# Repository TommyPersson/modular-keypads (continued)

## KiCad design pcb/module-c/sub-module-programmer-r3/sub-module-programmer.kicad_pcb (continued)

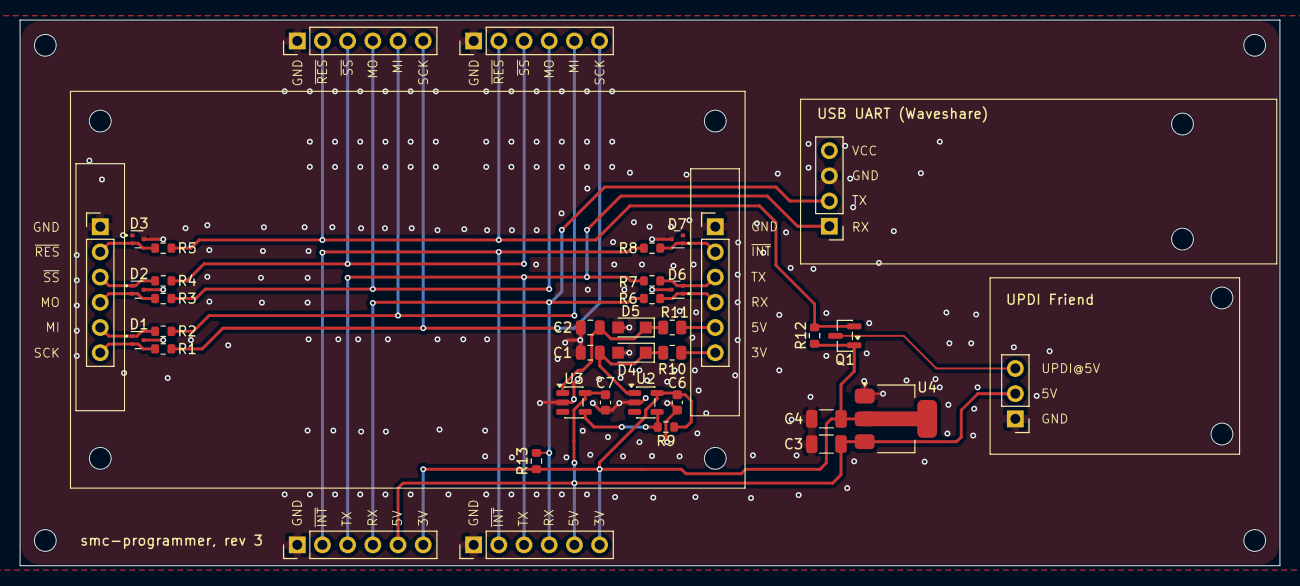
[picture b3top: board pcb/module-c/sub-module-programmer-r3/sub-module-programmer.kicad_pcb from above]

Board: 4 copper layers, 127.0 x 55.0 mm, 50 parts (0 on the bottom side), 25 nets.

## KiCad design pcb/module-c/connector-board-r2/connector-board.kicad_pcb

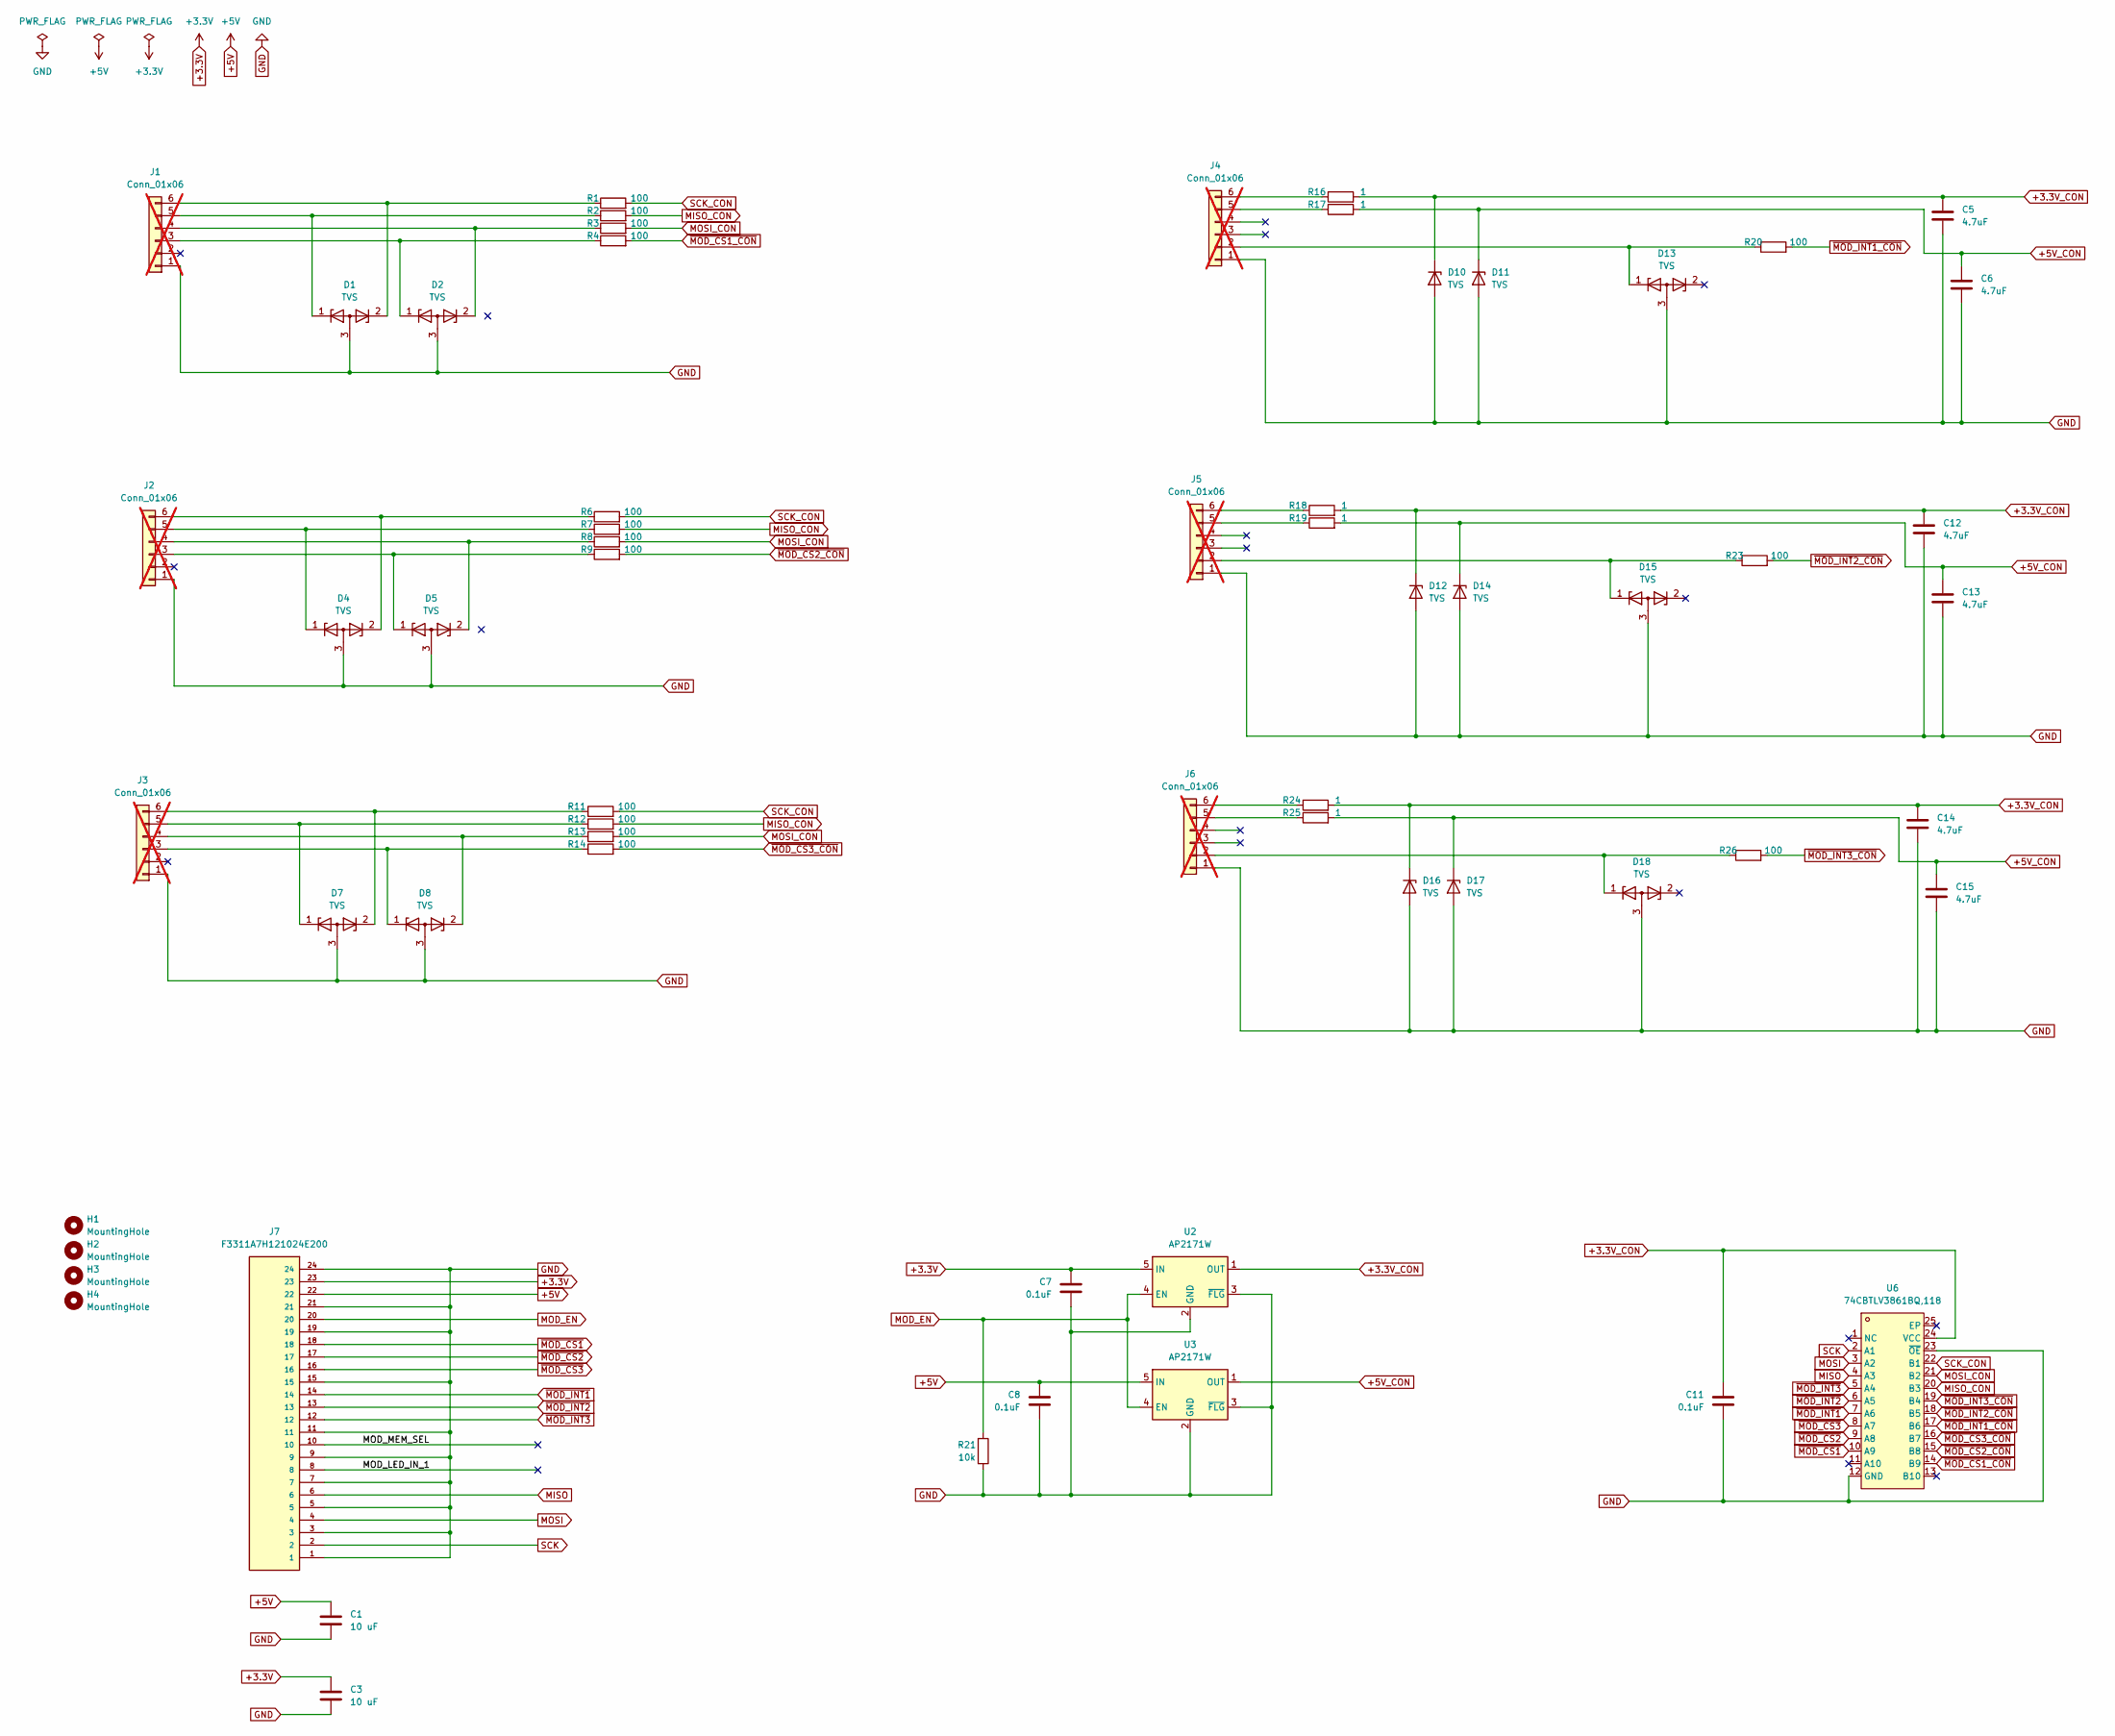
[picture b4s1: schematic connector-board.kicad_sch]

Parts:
C1, C3: 10 uF; C_1206_3216Metric
C5, C6, C12, C13, C14, C15: 4.7uF; C_0805_2012Metric
C7, C8, C11: 0.1uF; C_0603_1608Metric
D1, D2, D4, D5, D7, D8, D13, D15, D18: TVS; SOT-723
D10, D11, D12, D14, D16, D17: TVS; Nexperia_CFP3_SOD-123W
H1, H2, H3, H4: MountingHole; MountingHole_2.2mm_M2
J1, J2, J3, J4, J5, J6: Conn_01x06; PinHeader_1x06_P2.54mm_Vertical; not fitted
J7: F3311A7H121024E200; AMPHENOL_F3311A7H121024E200; PARTREV A
R1, R2, R3, R4, R6, R7, R8, R9, R11, R12, R13, R14, R20, R23, R26: 100; R_0603_1608Metric
R16, R17, R18, R19, R24, R25: 1; R_0805_2012Metric
R21: 10k; R_0603_1608Metric
U2, U3: AP2171W; SOT-23-5
U6: 74CBTLV3861BQ,118; DHVQFN24_L5.5-W3.5-P0.50-BL-EP; MPN 74CBTLV3861BQ,118; LCSC Part C458760

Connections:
+3.3V: C3.1, C7.1, J7.23, U2.5 (IN)
+3.3V_CON: C5.1, C11.1, C12.1, C14.1, D10.1 (K), D12.1 (K), D16.1 (K), R16.2, R18.2, R24.2, U2.1 (OUT), U6.24 (VCC)
+5V: C1.1, C8.1, J7.22, U3.5 (IN)
+5V_CON: C6.1, C13.1, C15.1, D11.1 (K), D14.1 (K), D17.1 (K), R17.2, R19.2, R25.2, U3.1 (OUT)
/MOD_LED_IN_1: J7.8
/MOD_MEM_SEL: J7.10
GND: C1.2, C3.2, C5.2, C6.2, C7.2, C8.2, C11.2, C12.2, C13.2, C14.2, C15.2, D1.3 (A), D2.3 (A), D4.3 (A), D5.3 (A), D7.3 (A), D8.3 (A), D10.2 (A), D11.2 (A), D12.2 (A), D13.3 (A), D14.2 (A), D15.3 (A), D16.2 (A), D17.2 (A), D18.3 (A), J1.1, J2.1, J3.1, J4.1, J5.1, J6.1, J7.1, J7.3, J7.5, J7.7, J7.9, J7.11, J7.15, J7.19, J7.21, J7.24, R21.1, U2.2 (GND), U2.3 (~FLG), U3.2 (GND), U3.3 (~FLG), U6.12 (GND), U6.23 (~OE)
MISO: J7.6, U6.4 (A3)
MISO_CON: R2.2, R7.2, R12.2, U6.20 (B3)
MOD_EN: J7.20, R21.2, U2.4 (EN), U3.4 (EN)
MOSI: J7.4, U6.3 (A2)
MOSI_CON: R3.2, R8.2, R13.2, U6.21 (B2)
unnamed: D2.1 (K), J1.3, R4.1
unnamed: D2.2 (K), J1.4, R3.1
unnamed: D1.1 (K), J1.5, R2.1
unnamed: D1.2 (K), J1.6, R1.1
unnamed: D5.1 (K), J2.3, R9.1
unnamed: D5.2 (K), J2.4, R8.1
unnamed: D4.1 (K), J2.5, R7.1
unnamed: D4.2 (K), J2.6, R6.1
unnamed: D8.1 (K), J3.3, R14.1
unnamed: D8.2 (K), J3.4, R13.1
unnamed: D7.1 (K), J3.5, R12.1
unnamed: D7.2 (K), J3.6, R11.1
unnamed: D13.1 (K), J4.2, R20.1
unnamed: J4.5, R17.1
unnamed: J4.6, R16.1
unnamed: D15.1 (K), J5.2, R23.1
unnamed: J5.5, R19.1
unnamed: J5.6, R18.1
unnamed: D18.1 (K), J6.2, R26.1
unnamed: J6.5, R25.1
unnamed: J6.6, R24.1
SCK: J7.2, U6.2 (A1)
SCK_CON: R1.2, R6.2, R11.2, U6.22 (B1)
~MOD_CS1_CON: R4.2, U6.14 (B9)
~MOD_CS1: J7.18, U6.10 (A9)
~MOD_CS2_CON: R9.2, U6.15 (B8)
~MOD_CS2: J7.17, U6.9 (A8)
~MOD_CS3_CON: R14.2, U6.16 (B7)
~MOD_CS3: J7.16, U6.8 (A7)
~MOD_INT1_CON: R20.2, U6.17 (B6)
~MOD_INT1: J7.14, U6.7 (A6)
~MOD_INT2_CON: R23.2, U6.18 (B5)
~MOD_INT2: J7.13, U6.6 (A5)
~MOD_INT3_CON: R26.2, U6.19 (B4)
~MOD_INT3: J7.12, U6.5 (A4)

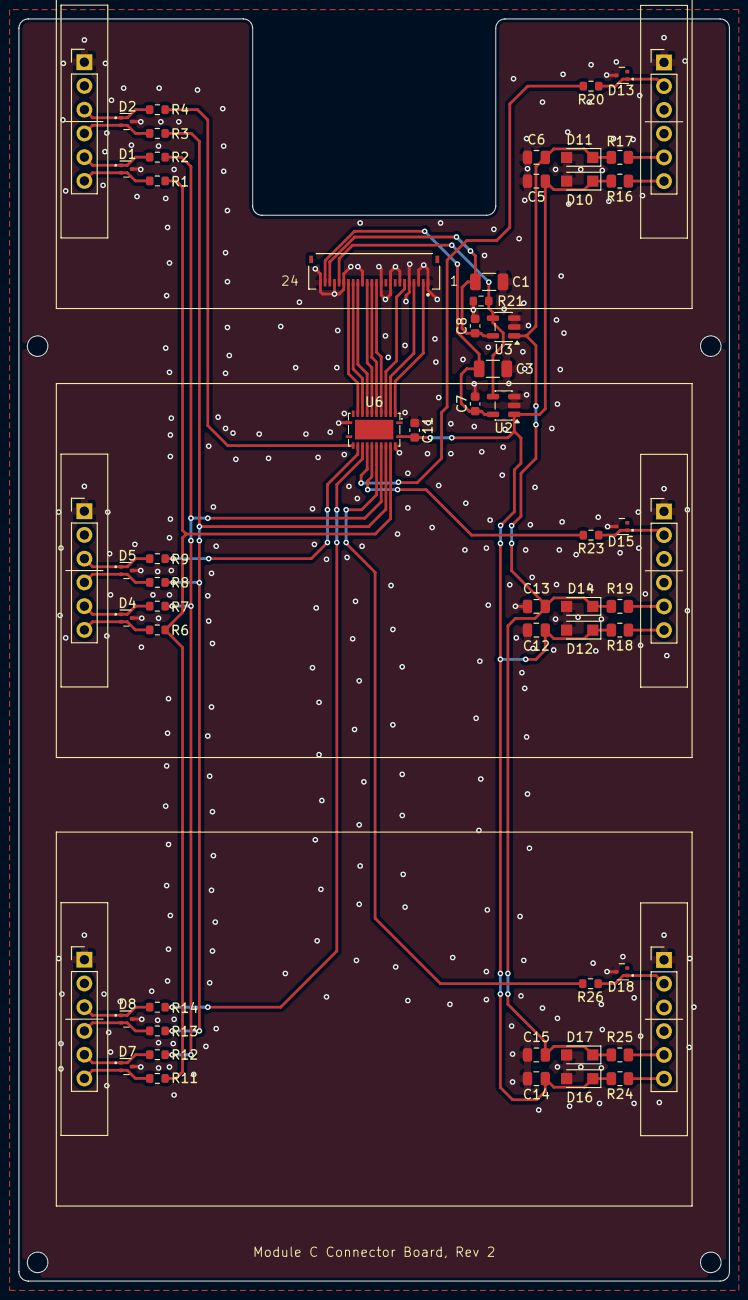
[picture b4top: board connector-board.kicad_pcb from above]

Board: 2 copper layers, 76.0 x 135.0 mm, 62 parts (0 on the bottom side), 45 nets.

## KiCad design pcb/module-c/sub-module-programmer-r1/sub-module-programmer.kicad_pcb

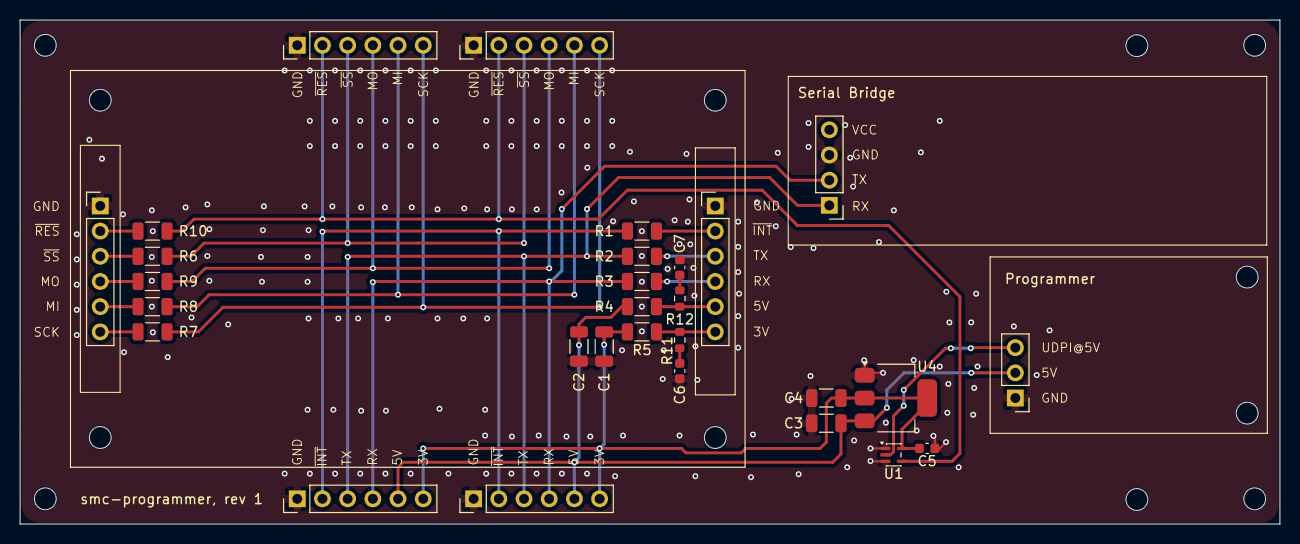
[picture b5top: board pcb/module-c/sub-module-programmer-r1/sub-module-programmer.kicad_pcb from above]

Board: 2 copper layers, 127.0 x 50.8 mm, 41 parts (0 on the bottom side), 24 nets.

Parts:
C1, C2: 10uF; C_1206_3216Metric
C3: 10 uF; C_1206_3216Metric
C4: 22 uF; C_1206_3216Metric
C5: 0.1 uF; C_0603_1608Metric
C6, C7: 0.1uF; C_0603_1608Metric
H1, H2, H3, H4, H5, H6, H7, H8, H9, H10, H11, H12: MountingHole; MountingHole_2.2mm_M2
J1, J3, J4, J5, J6, J7: Conn_01x06; PinHeader_1x06_P2.54mm_Vertical
J2: Conn_01x03; PinHeader_1x03_P2.54mm_Vertical
J8: Serial Bridge; PinHeader_1x04_P2.54mm_Vertical
R1, R2, R3, R6: 1k; R_1206_3216Metric
R4, R5: 4.7; R_1206_3216Metric
R7, R8, R9: 220; R_1206_3216Metric
R10: 100; R_1206_3216Metric
R11, R12: 2.2; R_0603_1608Metric
U1: 74AHCT1G125; SOT-353_SC-70-5
U4: LD1117S33TR_SOT223; SOT-223-3_TabPin2

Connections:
+3.3V: C1.1, C4.1, C5.1, J5.6, J7.6, R5.2, U1.5 (VCC), U4.2 (VO)
+5V: C2.1, C3.1, J2.2, J5.5, J7.5, R4.2, U4.3 (VI)
BRIDGE_RX: J5.3, J7.3, J8.1, R2.2
BRIDGE_TX: J5.4, J7.4, J8.2, R3.2
GND: C1.2, C2.2, C3.2, C4.2, C5.2, C6.2, C7.2, J1.1, J2.1, J3.1, J4.1, J5.1, J6.1, J7.1, J8.3, U1.1, U1.3 (GND), U4.1 (GND)
MISO: J4.5, J6.5, R8.2
MOSI: J4.4, J6.4, R9.2
unnamed: C6.1, R11.1
unnamed: C7.1, R12.1
unnamed: J1.2, R1.1
unnamed: J1.3, R2.1
unnamed: J1.4, R3.1
unnamed: J1.5, R4.1, R12.2
unnamed: J1.6, R5.1, R11.2
unnamed: J3.2, R10.1
unnamed: J3.3, R6.1
unnamed: J3.4, R9.1
unnamed: J3.5, R8.1
unnamed: J3.6, R7.1
SCK: J4.6, J6.6, R7.2
UPDI@5V: J2.3, U1.2
~INT: J5.2, J7.2, R1.2
~RESET: J4.2, J6.2, R10.2, U1.4
~SS: J4.3, J6.3, R6.2

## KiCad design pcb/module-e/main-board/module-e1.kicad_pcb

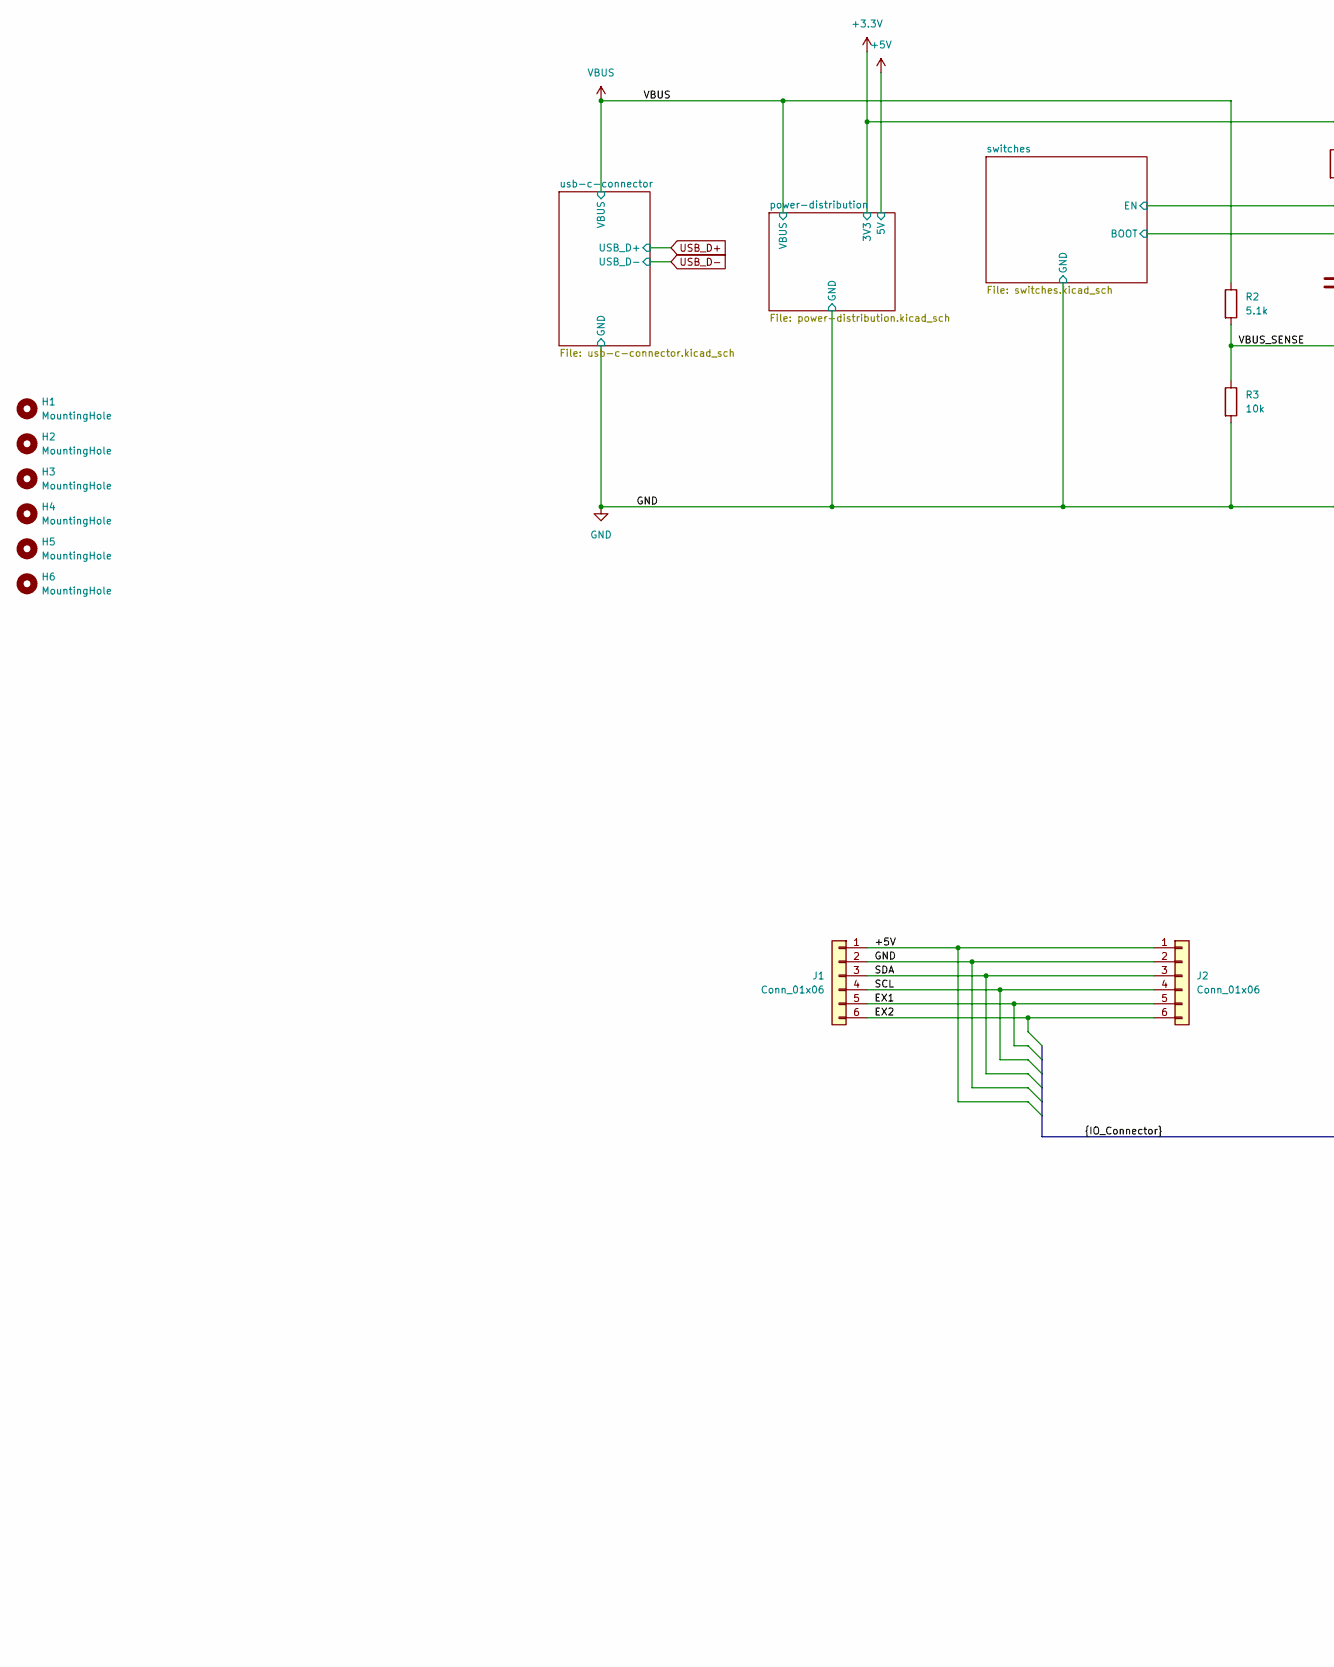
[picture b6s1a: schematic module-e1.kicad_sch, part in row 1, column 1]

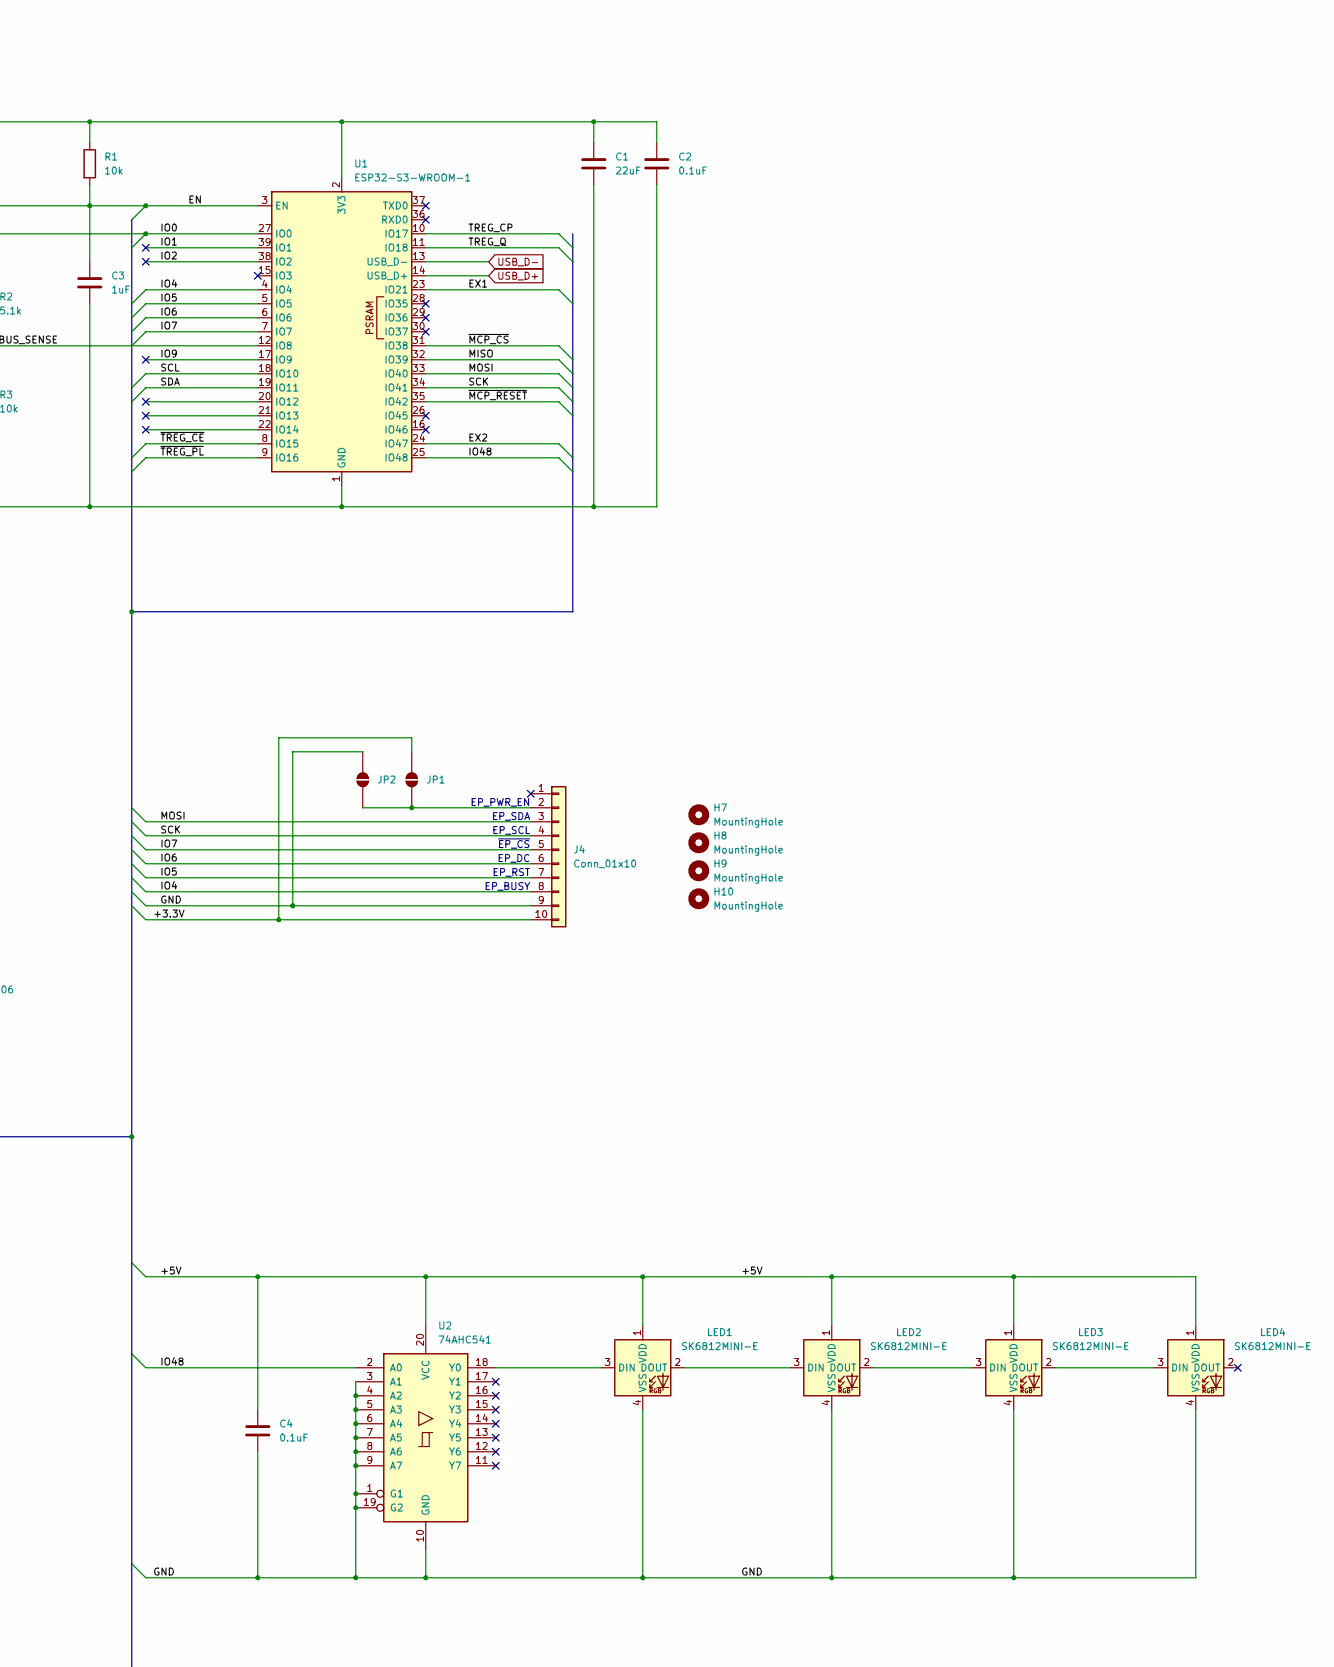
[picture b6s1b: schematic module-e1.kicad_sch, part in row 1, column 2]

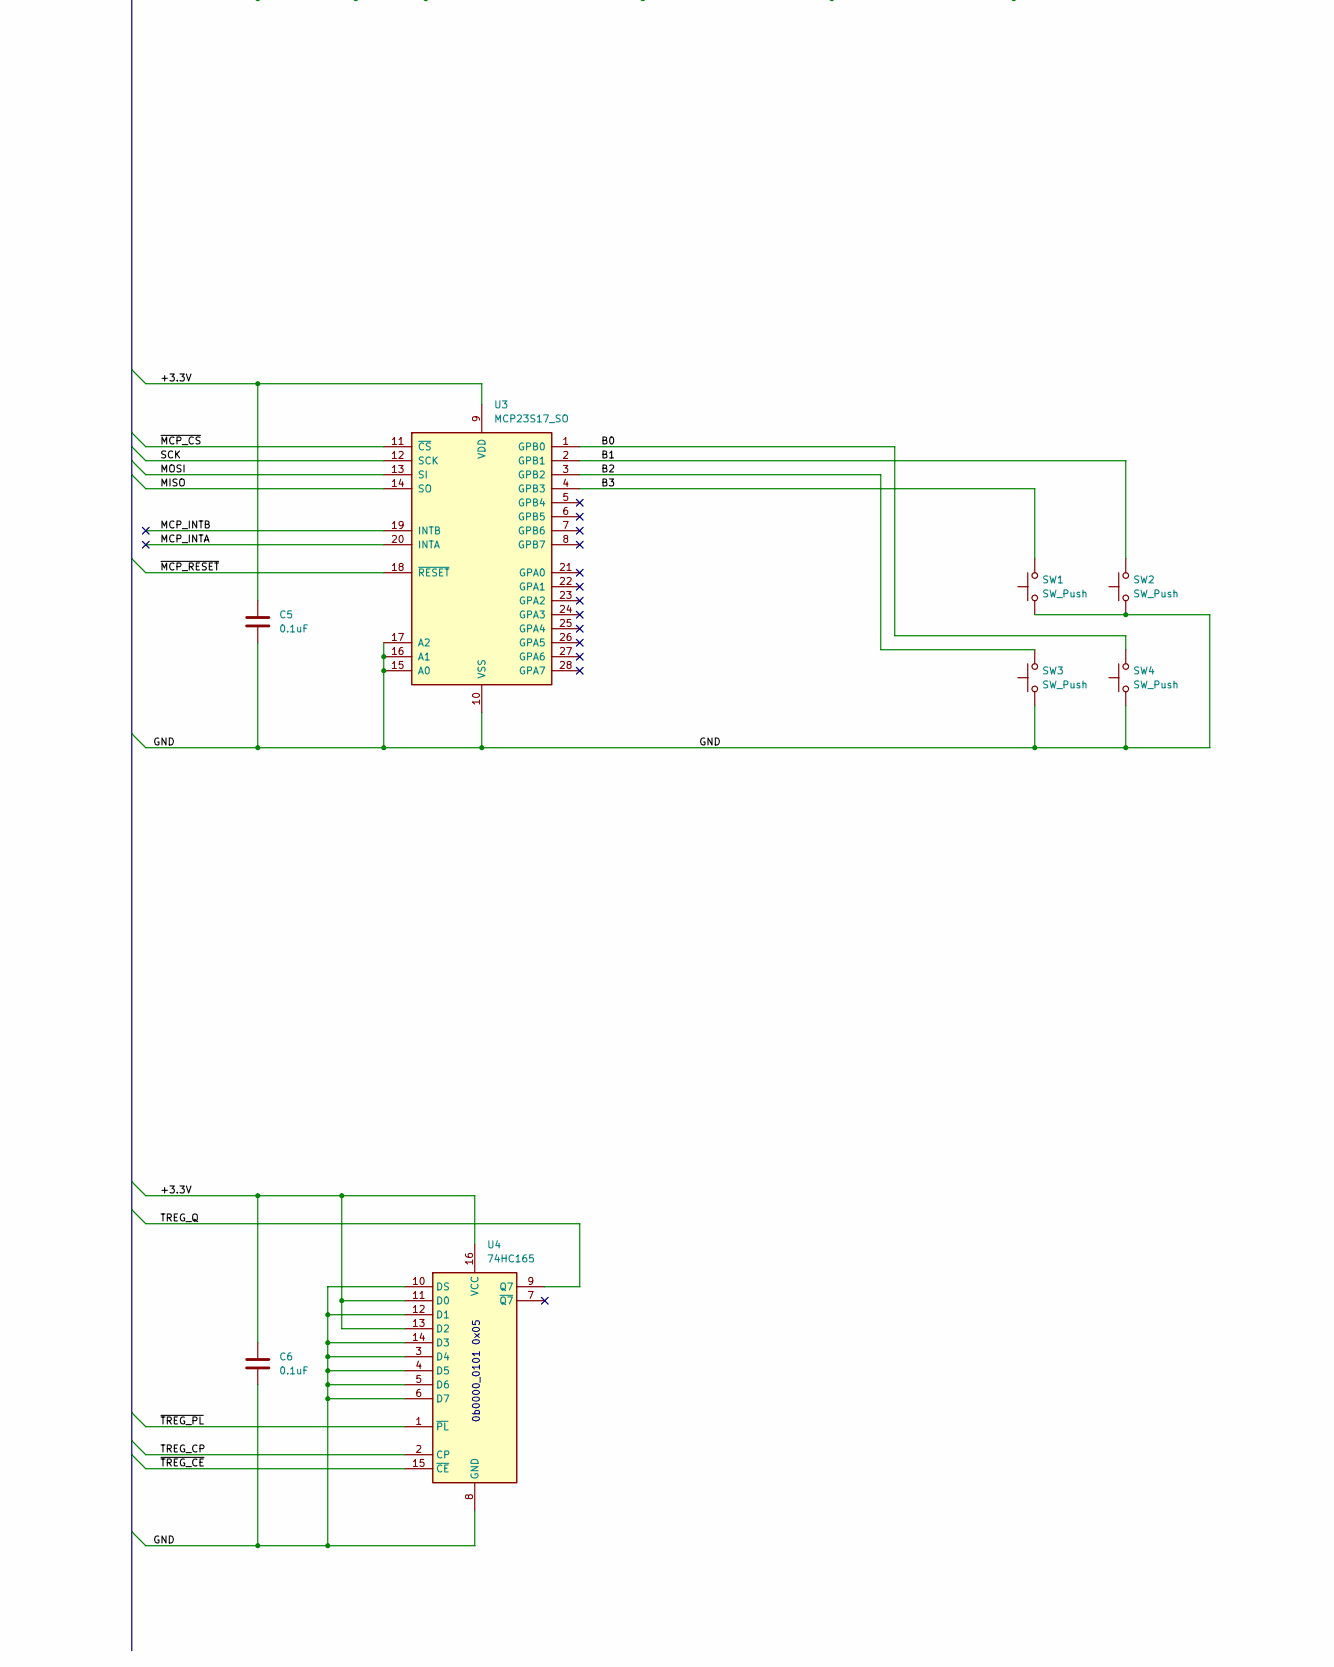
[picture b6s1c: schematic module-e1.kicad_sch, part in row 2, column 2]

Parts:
C1: 22uF; C_1206_3216Metric_Pad1.33x1.80mm_HandSolder
C2, C4, C5, C6: 0.1uF; C_1206_3216Metric_Pad1.33x1.80mm_HandSolder
C3: 1uF; C_1206_3216Metric_Pad1.33x1.80mm_HandSolder
H1, H2, H3, H4, H5, H6, H7, H8, H9, H10: MountingHole; MountingHole_2.2mm_M2
J1: Conn_01x06; PinSocket_1x06_P2.54mm_MagPogoHor_R
J2: Conn_01x06; PinSocket_1x06_P2.54mm_MagPogoHor
J4: Conn_01x10; AMPHENOL_F3311A7H121010E200
JP1, JP2: SolderJumper-2_P1.3mm_Open_TrianglePad1.0x1.5mm
LED1, LED2, LED3, LED4: SK6812MINI-E; LED_choc_6028R-ROT
R1, R3: 10k; R_1206_3216Metric_Pad1.30x1.75mm_HandSolder
R2: 5.1k; R_1206_3216Metric_Pad1.30x1.75mm_HandSolder
SW1, SW2, SW3, SW4: SW_Push; SW_Hotswap_Kailh_Choc_V1_1.50u
U1: ESP32-S3-WROOM-1; ESP32-S3-WROOM-1U
U2: 74AHC541; SOIC-20W_7.5x12.8mm_P1.27mm
U3: MCP23S17_SO; SOIC-28W_7.5x17.9mm_P1.27mm
U4: 74HC165; SOIC-16_3.9x9.9mm_P1.27mm

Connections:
+3.3V: C1.1, C2.1, C5.1, C6.1, J4.10, JP1.2 (B), R1.1, U1.2 (3V3), U3.9 (VDD), U4.11 (D0), U4.13 (D2), U4.16 (VCC); also elsewhere on the board
+5V: C4.1, J1.1, J2.1, LED1.1 (VDD), LED2.1 (VDD), LED3.1 (VDD), LED4.1 (VDD), U2.20 (VCC); also elsewhere on the board
/B0: SW4.2, U3.1 (GPB0)
/B1: SW2.2, U3.2 (GPB1)
/B2: SW3.2, U3.3 (GPB2)
/B3: SW1.2, U3.4 (GPB3)
/EN: C3.1, R1.2, U1.3 (EN); also elsewhere on the board
/EX1: J1.5, J2.5, U1.23 (IO21)
/EX2: J1.6, J2.6, U1.24 (IO47)
/IO0: U1.27 (IO0); also elsewhere on the board
/IO1: U1.39 (IO1)
/IO2: U1.38 (IO2)
/IO4: J4.8, U1.4 (IO4)
/IO5: J4.7, U1.5 (IO5)
/IO6: J4.6, U1.6 (IO6)
/IO7: J4.5, U1.7 (IO7)
/IO9: U1.17 (IO9)
/IO48: U1.25 (IO48), U2.2 (A0)
/MCP_INTA: U3.20 (INTA)
/MCP_INTB: U3.19 (INTB)
/MISO: U1.32 (IO39), U3.14 (SO)
/MOSI: J4.3, U1.33 (IO40), U3.13 (SI)
/SCK: J4.4, U1.34 (IO41), U3.12 (SCK)
/SCL: J1.4, J2.4, U1.18 (IO10)
/SDA: J1.3, J2.3, U1.19 (IO11)
/TREG_CP: U1.10 (IO17), U4.2 (CP)
/TREG_Q: U1.11 (IO18), U4.9 (Q7)
/VBUS_SENSE: R2.2, R3.1, U1.12 (IO8)
/~MCP_CS: U1.31 (IO38), U3.11 (~CS)
/~MCP_RESET: U1.35 (IO42), U3.18 (~RESET)
/~TREG_CE: U1.8 (IO15), U4.15 (~CE)
/~TREG_PL: U1.9 (IO16), U4.1 (~PL)
GND: C1.2, C2.2, C3.2, C4.2, C5.2, C6.2, J1.2, J2.2, J4.9, JP2.2 (B), LED1.4 (VSS), LED2.4 (VSS), LED3.4 (VSS), LED4.4 (VSS), R3.2, SW1.1, SW2.1, SW3.1, SW4.1, U1.1 (GND), U1.40 (GND), U1.41 (GND), U2.1 (G1), U2.3 (A1), U2.4 (A2), U2.5 (A3), U2.6 (A4), U2.7 (A5), U2.8 (A6), U2.9 (A7), U2.10 (GND), U2.19 (G2), U3.10 (VSS), U3.15 (A0), U3.16 (A1), U3.17 (A2), U4.3 (D4), U4.4 (D5), U4.5 (D6), U4.6 (D7), U4.8 (GND), U4.10 (DS), U4.12 (D1), U4.14 (D3); also elsewhere on the board
unnamed: J4.2, JP1.1 (A), JP2.1 (A)
unnamed: LED1.3 (DIN), U2.18 (Y0)
unnamed: LED1.2 (DOUT), LED2.3 (DIN)
unnamed: LED2.2 (DOUT), LED3.3 (DIN)
unnamed: LED3.2 (DOUT), LED4.3 (DIN)
USB_D+: U1.14 (USB_D+); also elsewhere on the board
USB_D-: U1.13 (USB_D-); also elsewhere on the board
VBUS: R2.1; also elsewhere on the board

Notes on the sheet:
EP_DC
EP_PWR_EN
EP_RST
EP_SDA
EP_BUSY
0b0000_0101 0x05
~{EP_CS}
EP_SCL

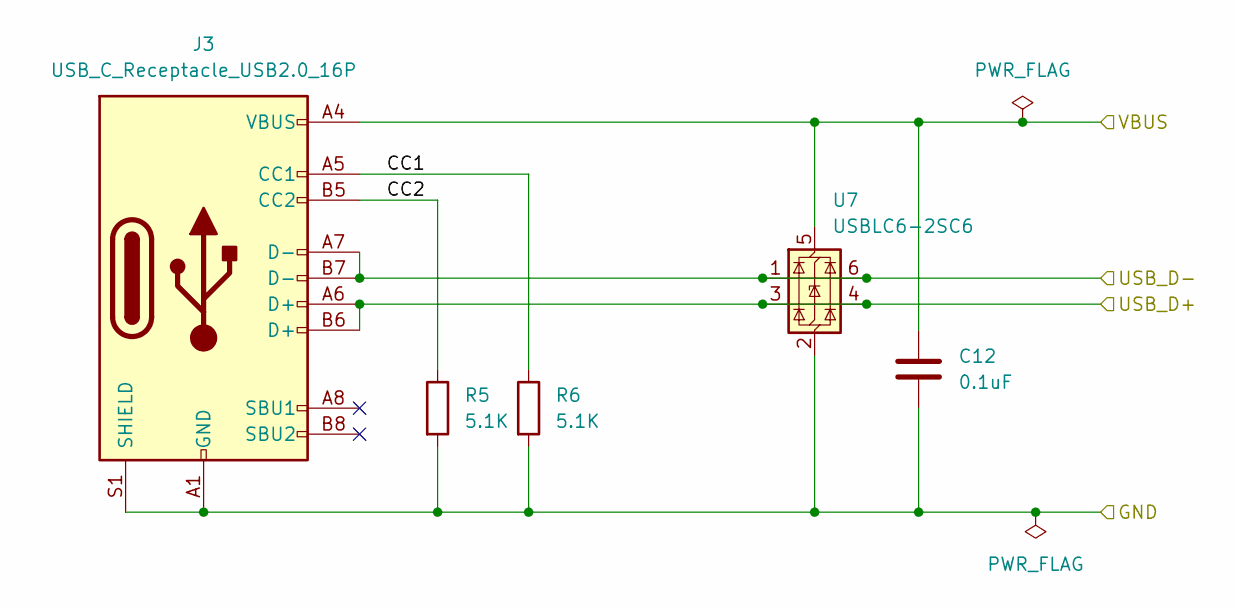
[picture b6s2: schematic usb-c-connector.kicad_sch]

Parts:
C12: 0.1uF; C_1206_3216Metric_Pad1.33x1.80mm_HandSolder
J3: USB_C_Receptacle_USB2.0_16P; USB_C_Receptacle_GCT_USB4105-xx-A_16P_TopMnt_Horizontal
R5, R6: 5.1K; R_1206_3216Metric_Pad1.30x1.75mm_HandSolder
U7: USBLC6-2SC6; SOT-23-6_Handsoldering

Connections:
/usb-c-connector/CC1: J3.A5 (CC1), R6.1
/usb-c-connector/CC2: J3.B5 (CC2), R5.1
GND: C12.2, J3.A1 (GND), J3.A12 (GND), J3.B1 (GND), J3.B12 (GND), J3.S1 (SHIELD), R5.2, R6.2, U7.2 (GND); also elsewhere on the board
USB_D+: J3.A6 (D+), J3.B6 (D+), U7.3 (I/O2), U7.4 (I/O2); also elsewhere on the board
USB_D-: J3.A7 (D-), J3.B7 (D-), U7.1 (I/O1), U7.6 (I/O1); also elsewhere on the board
VBUS: C12.1, J3.A4 (VBUS), J3.A9 (VBUS), J3.B4 (VBUS), J3.B9 (VBUS), U7.5 (VBUS); also elsewhere on the board

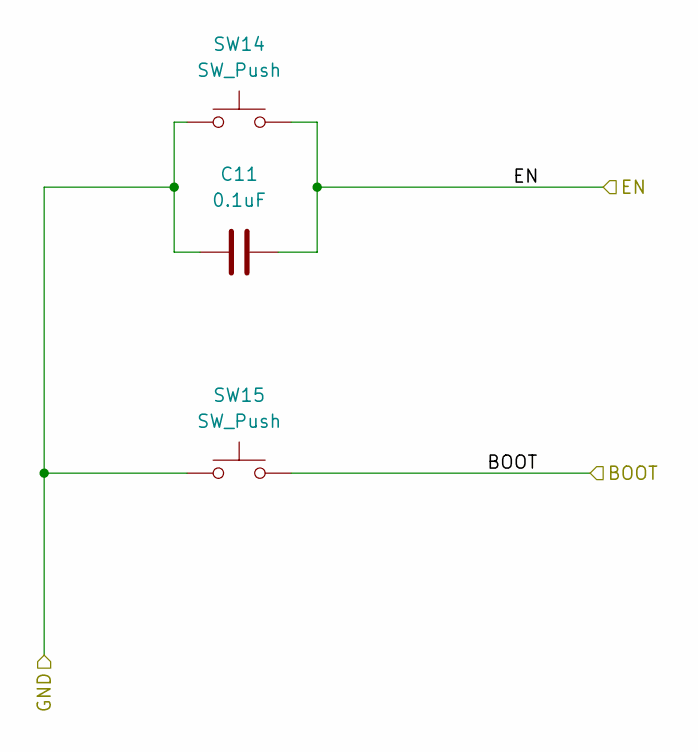
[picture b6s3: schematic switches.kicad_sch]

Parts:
C11: 0.1uF; C_1206_3216Metric_Pad1.33x1.80mm_HandSolder
SW14, SW15: SW_Push; Panasonic_EVQPUL_EVQPUC

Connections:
/EN: C11.2, SW14.2; also elsewhere on the board
/IO0: SW15.2; also elsewhere on the board
GND: C11.1, SW14.1, SW15.1; also elsewhere on the board

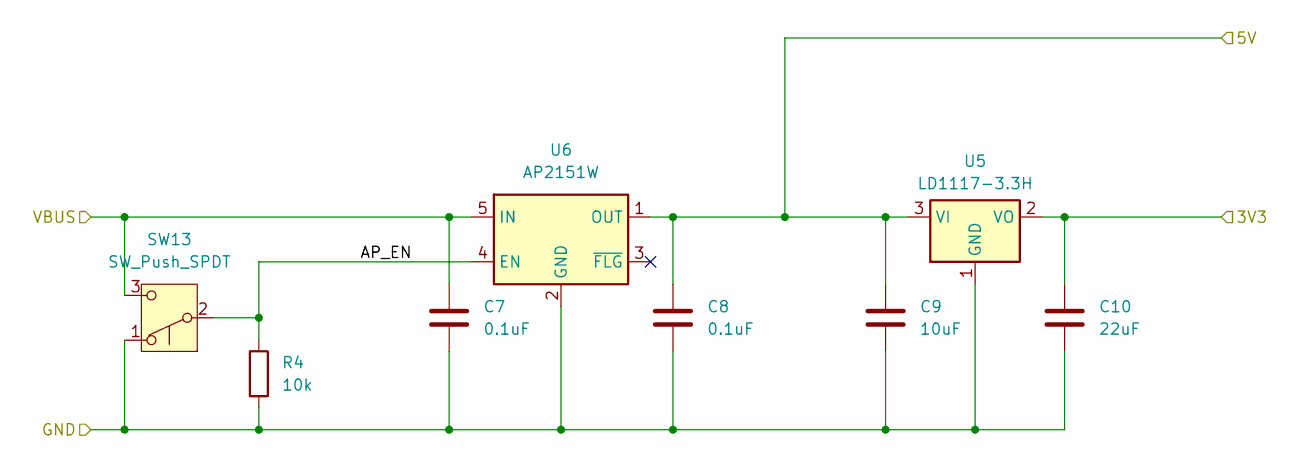
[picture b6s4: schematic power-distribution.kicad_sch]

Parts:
C7, C8: 0.1uF; C_1206_3216Metric_Pad1.33x1.80mm_HandSolder
C9: 10uF; C_1206_3216Metric_Pad1.33x1.80mm_HandSolder
C10: 22uF; C_1206_3216Metric_Pad1.33x1.80mm_HandSolder
R4: 10k; R_1206_3216Metric_Pad1.30x1.75mm_HandSolder
SW13: SW_Push_SPDT; SW_MSK12C02-HB
U5: LD1117-3.3H; SOT-223-3_TabPin2
U6: AP2151W; SOT-23-5_HandSoldering

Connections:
+3.3V: C10.1, U5.2 (VO); also elsewhere on the board
+5V: C8.1, C9.1, U5.3 (VI), U6.1 (OUT); also elsewhere on the board
/power-distribution/AP_EN: R4.1, SW13.2 (B), U6.4 (EN)
GND: C7.2, C8.2, C9.2, C10.2, R4.2, SW13.1 (A), U5.1 (GND), U6.2 (GND); also elsewhere on the board
VBUS: C7.1, SW13.3 (C), U6.5 (IN); also elsewhere on the board

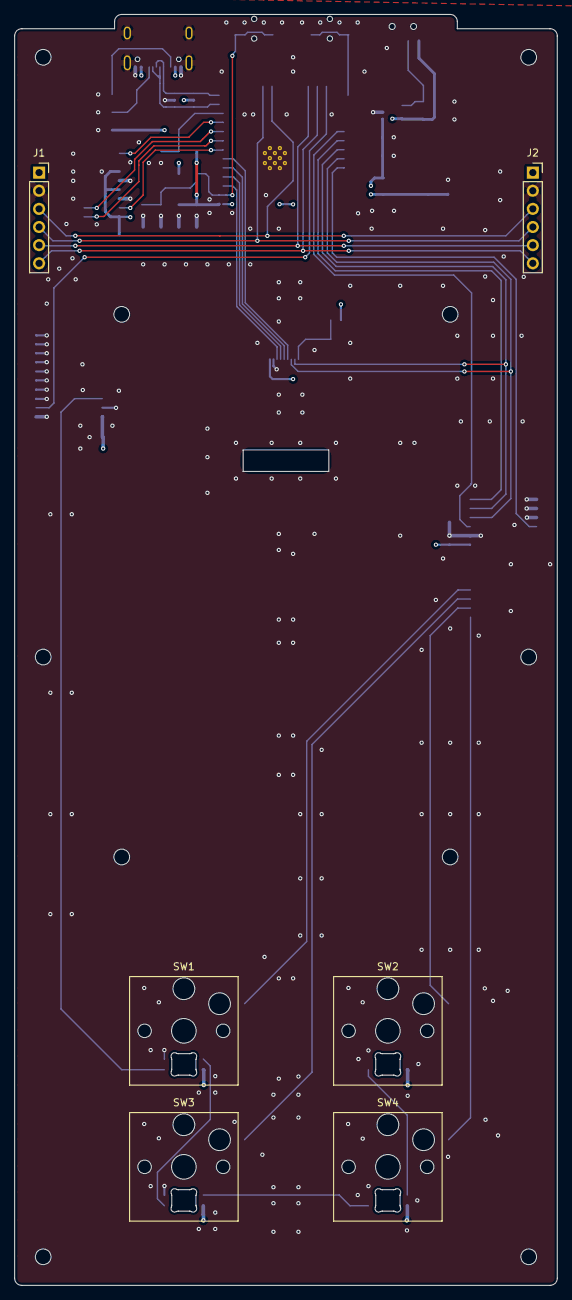
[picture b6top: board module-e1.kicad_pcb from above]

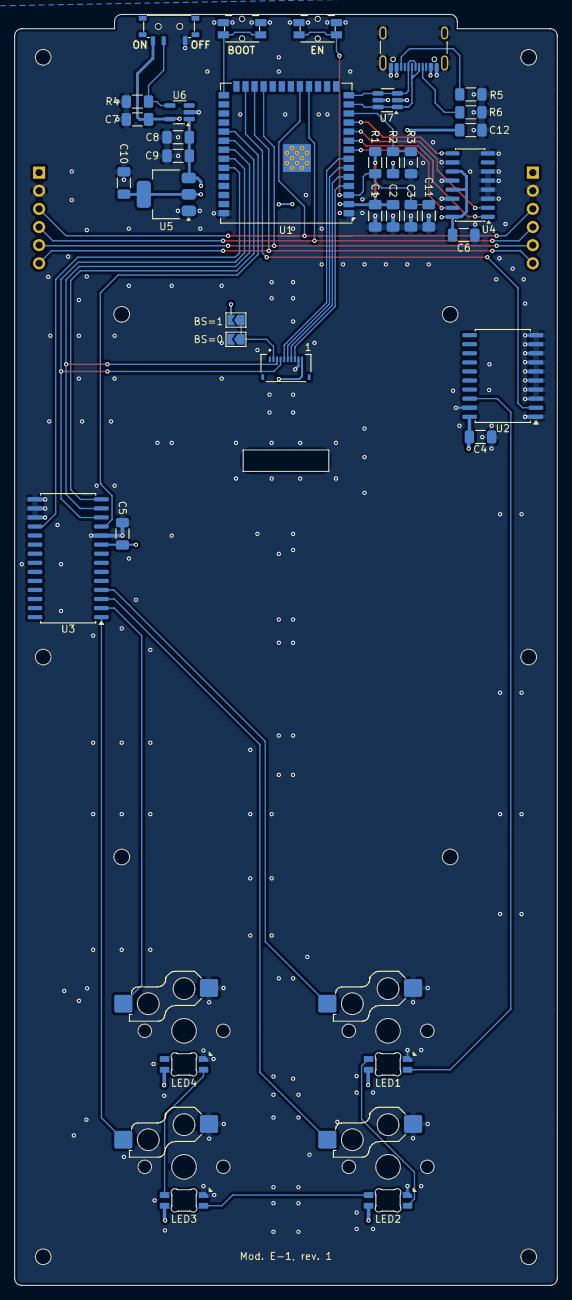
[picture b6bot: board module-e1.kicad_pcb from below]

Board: 4 copper layers, 76.0 x 178.0 mm, 52 parts (36 on the bottom side), 39 nets.
